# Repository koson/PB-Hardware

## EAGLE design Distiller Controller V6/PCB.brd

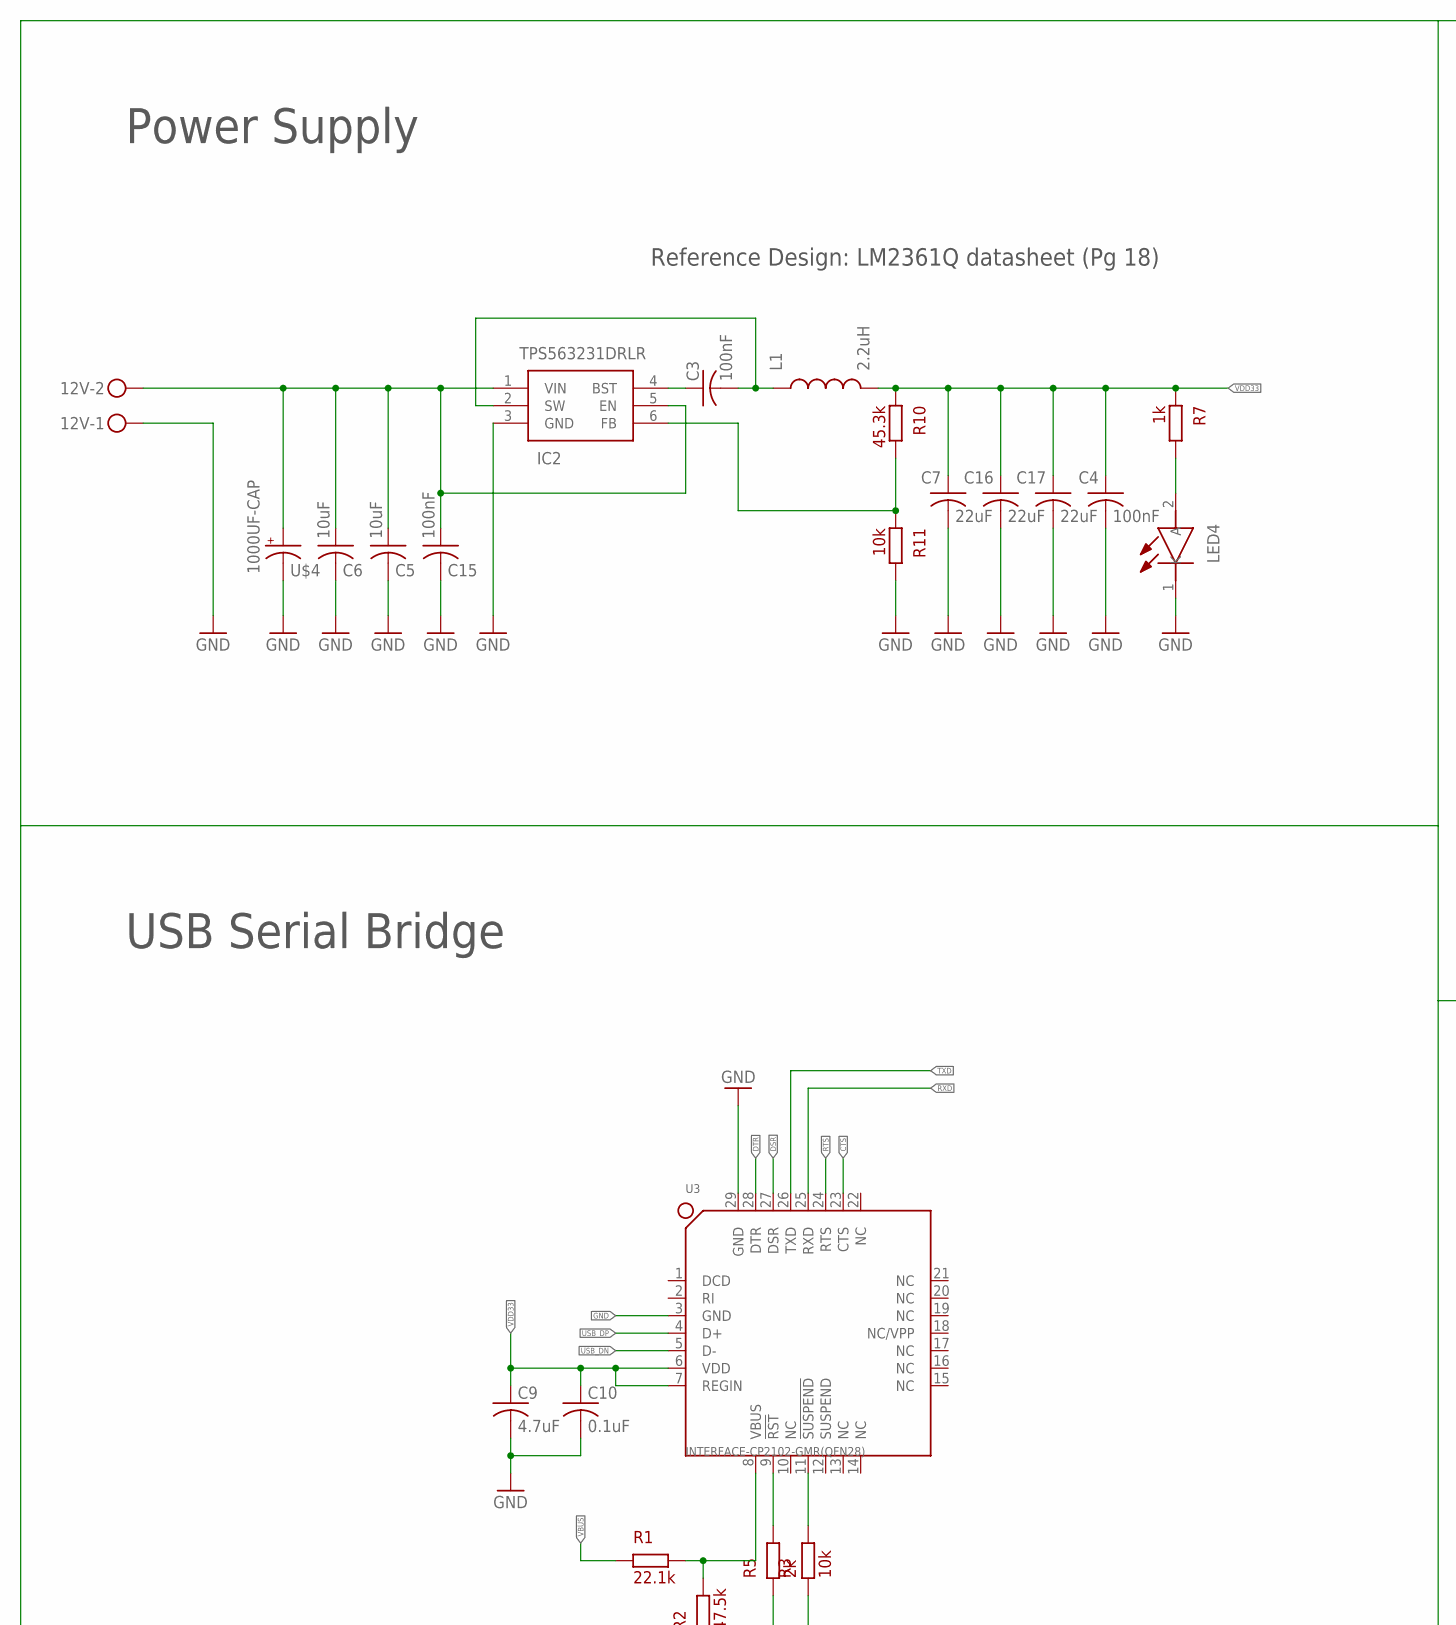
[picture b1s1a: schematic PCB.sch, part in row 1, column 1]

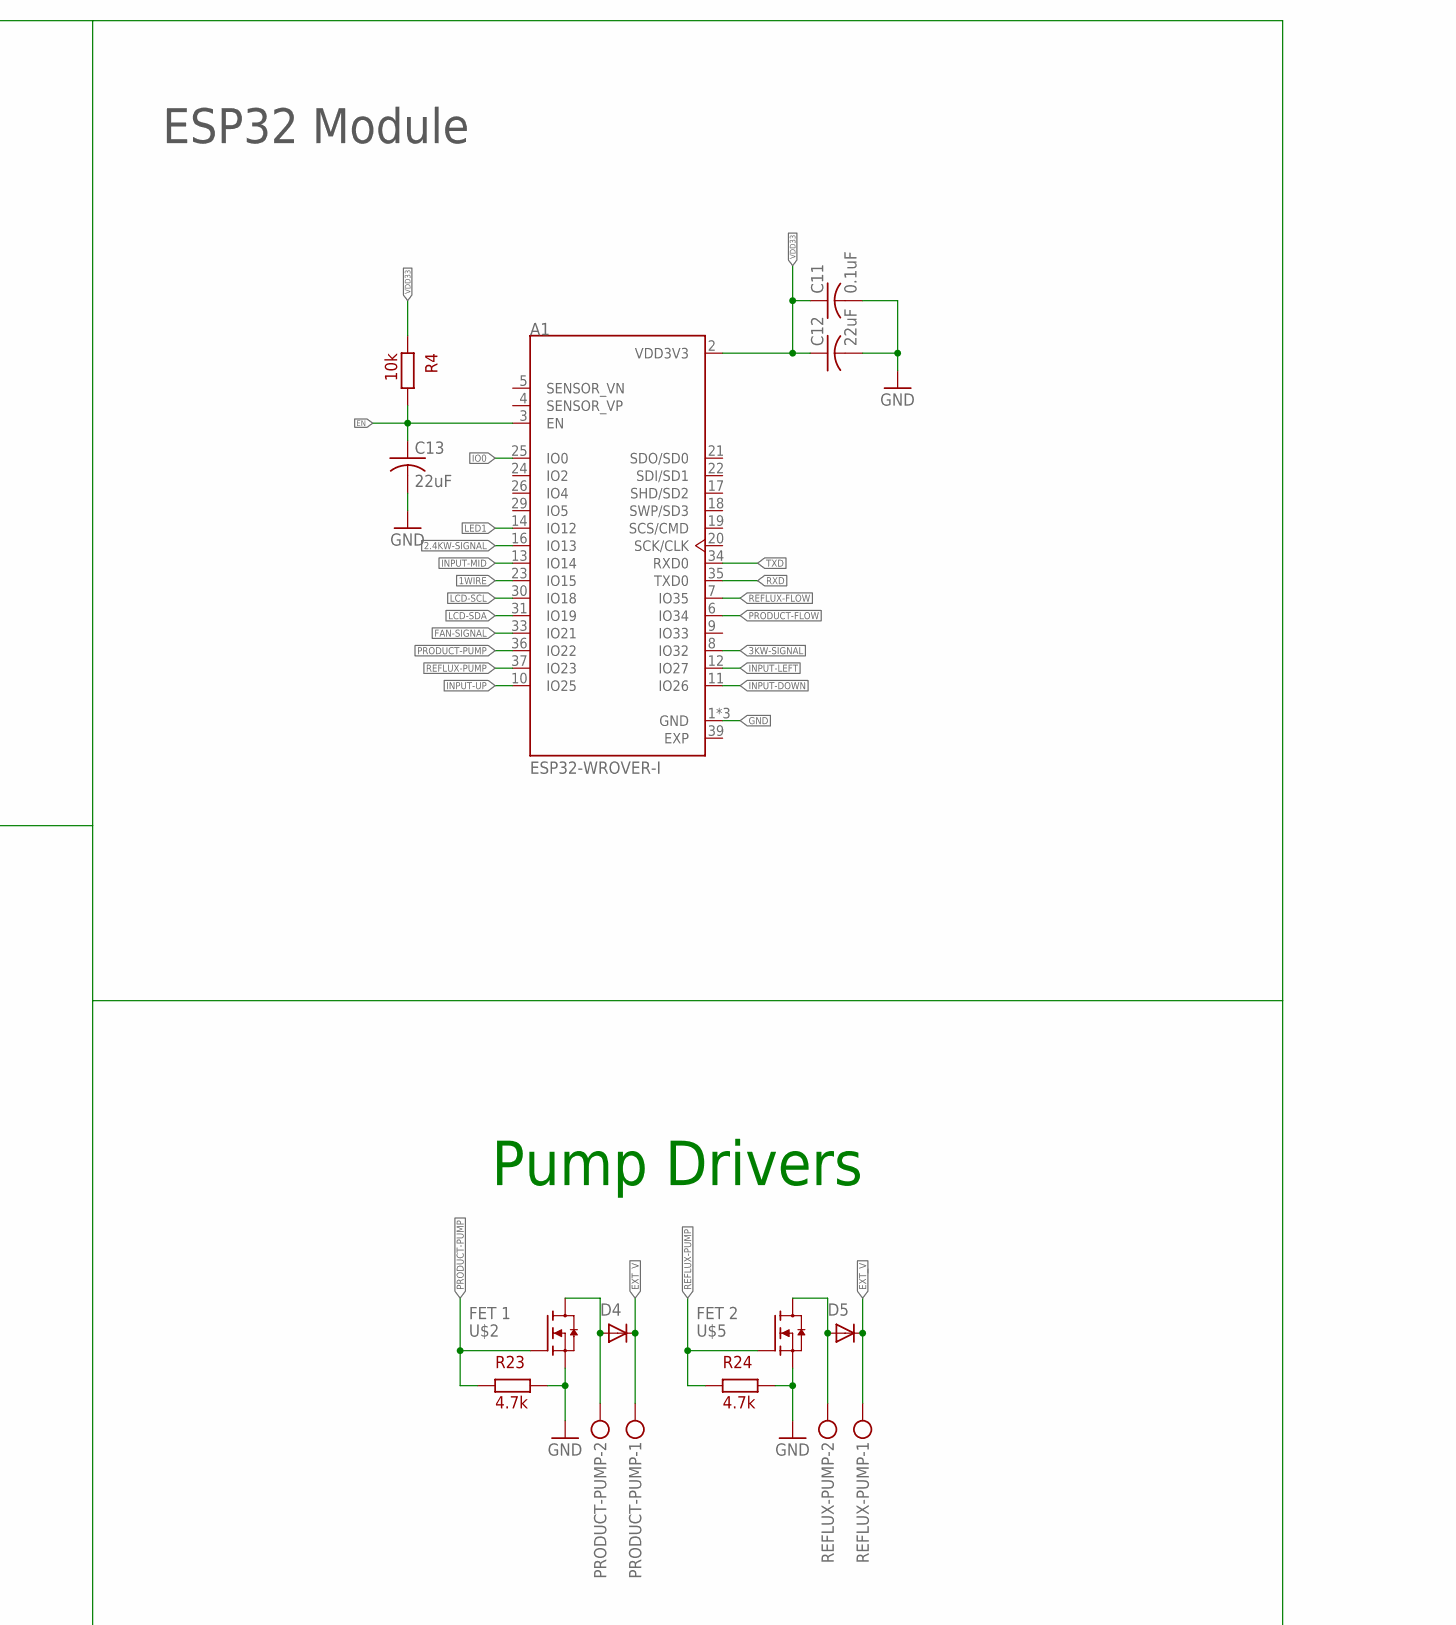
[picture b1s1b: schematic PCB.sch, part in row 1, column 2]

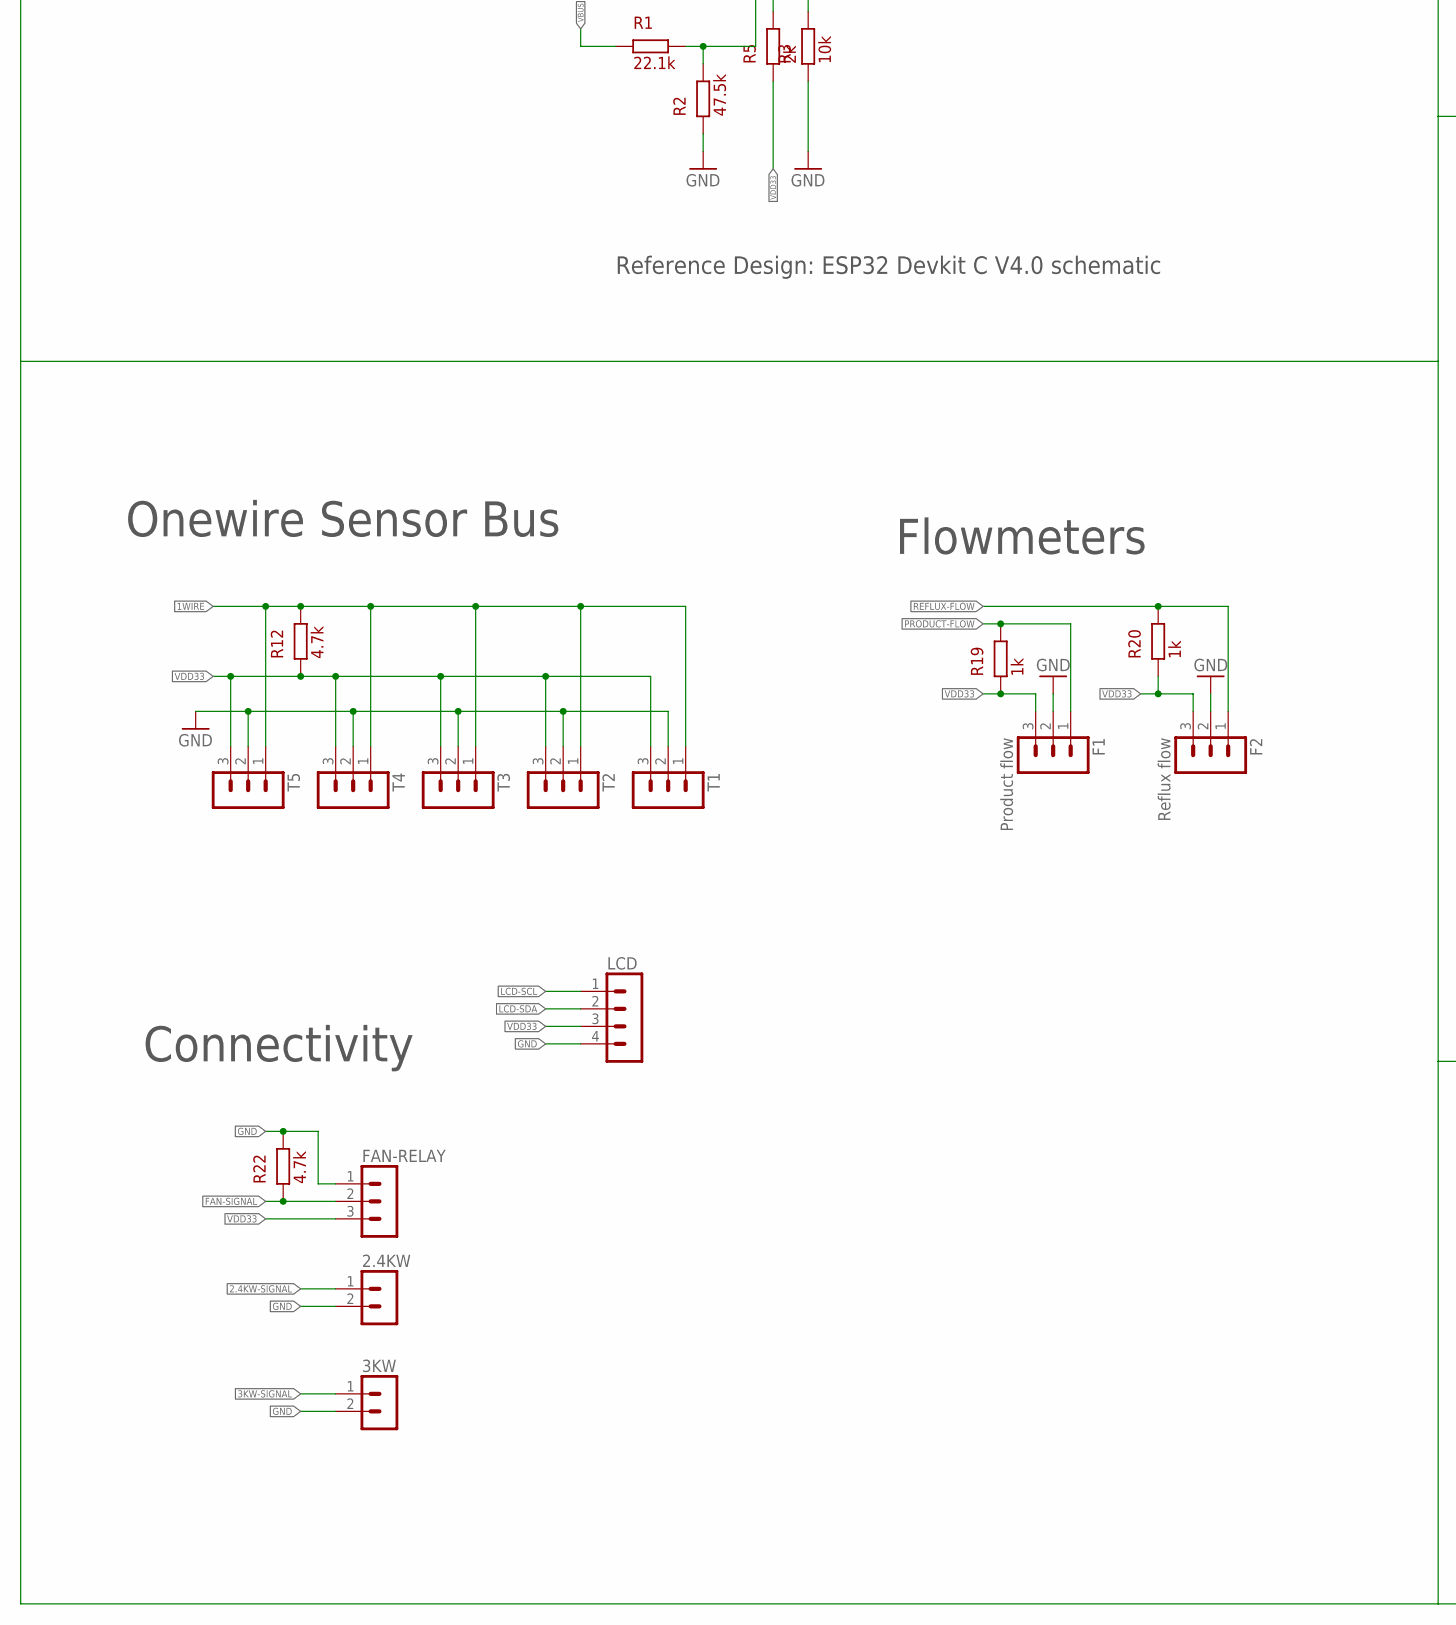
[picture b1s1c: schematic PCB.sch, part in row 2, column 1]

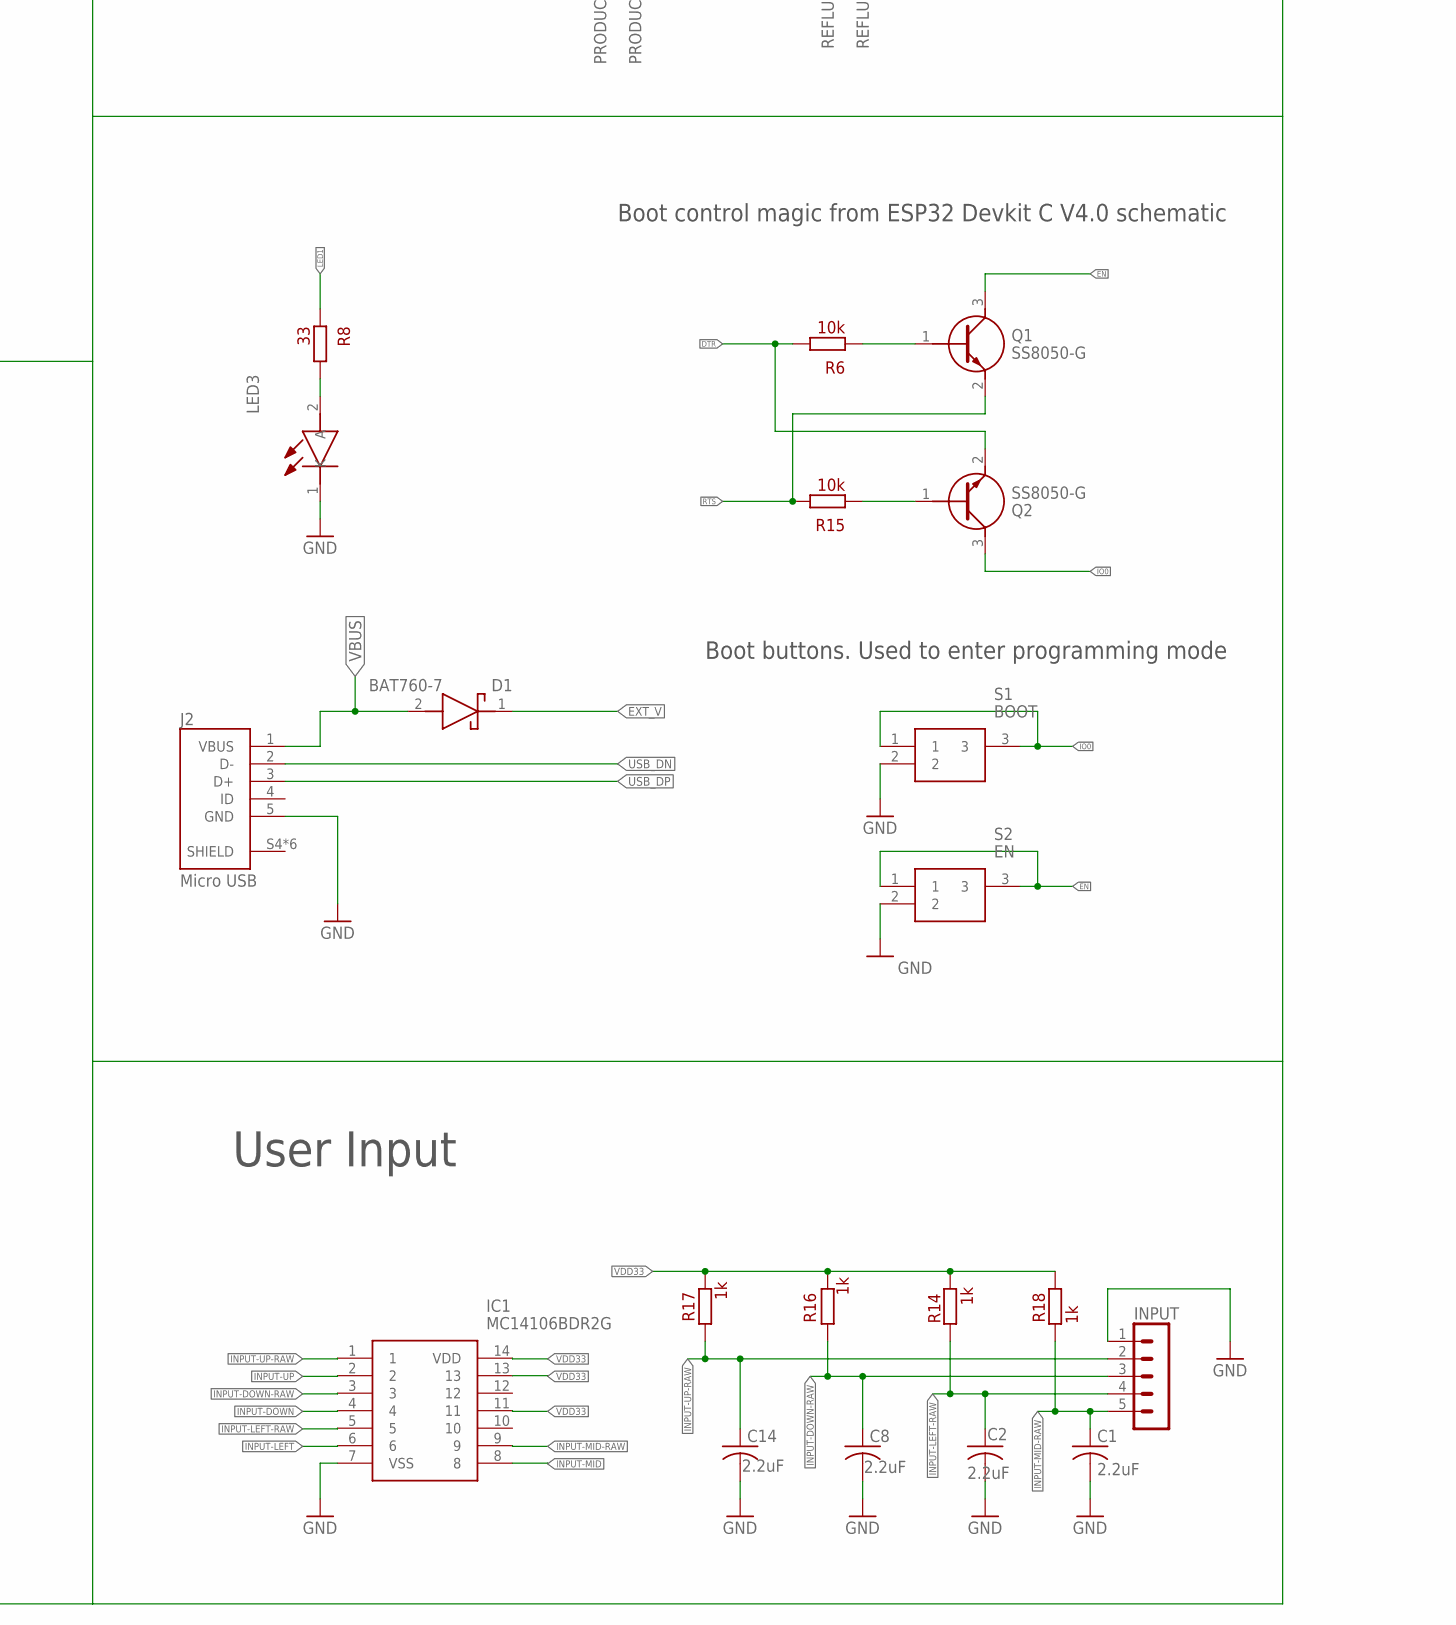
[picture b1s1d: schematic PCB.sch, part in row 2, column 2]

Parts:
2.4KW, 3KW: 53398-0210
12V: MKDSN1,5/2-5,08
A1: ESP32-WROVER-I; XCVR_ESP32-WROVER-I
C1, C2, C8, C14: 2.2uF; C0805K
C3, C4, C15: 100nF; C0805K
C5, C6: 10uF; C0805K
C7, C12, C13, C16, C17: 22uF; C0805K
C9: 4.7uF; C0805K
C10, C11: 0.1uF; C0805K
D1: BAT760-7; SOD2513X120N
D4, D5: RB095BGE-40TL; TO252; MPN PWR163S-25-2R20JE
F1: Product flow; 53398-0310
F2: Reflux flow; 53398-0310
FAN-RELAY: 53398-0310
IC1: MC14106BDR2G; SOIC127P600X175-14N
IC2: TPS563231DRLR; SOTFL50P160X60-6N
INPUT: 53398-0510
J2: Micro USB; TE_2040002-1
L1: 2.2uH; LB3218T2R2M
LCD: 53398-0410
LED3, LED4: SML-H12V8TT86C; LEDC2012X80N
PRODUCT-PUMP: MKDSN1,5/2-5,08
Q1, Q2: SS8050-G; SOT95P240X115-3N
R1: 22.1k; C0805K
R2: 47.5k; C0805K
R3, R4, R6, R11, R15: 10k; C0805K
R5: 2k; C0805K
R7, R14, R16, R17, R18, R19, R20: 1k; C0805K
R8: 33; C0805K
R10: 45.3k; C0805K
R12, R22, R23, R24: 4.7k; C0805K
REFLUX-PUMP: MKDSN1,5/2-5,08
S1: BOOT; TL3340
S2: EN; TL3340
T1, T2, T3, T4, T5: 53398-0310
U3: INTERFACE-CP2102-GMR(QFN28); QFN28G_0.5-5X5MM
U$2: FET 1; TO252
U$4: 1000UF-CAP; UNITED-CHEMICON-SMD-CAP-1000UF
U$5: FET 2; TO252

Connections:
1WIRE: A1.23 (IO15), R12.2, T1.1, T2.1, T3.1, T4.1, T5.1
2.4KW-SIGNAL: 2.4KW.1, A1.16 (IO13)
3KW-SIGNAL: 3KW.1, A1.8 (IO32)
BST: C3.1, IC2.4 (BST)
CTS: U3.23 (CTS)
DSR: U3.27 (DSR)
DTR: Q2.2 (E), R6.2, U3.28 (DTR)
EN: A1.3 (EN), C13.1, Q1.3 (C), R4.2, S2.1, S2.3
EXP: A1.39 (EXP)
EXT_V: 12V.2, C5.1, C6.1, C15.1, D1.1 (K), D4.2 (C), D5.2 (C), IC2.1 (VIN), IC2.5 (EN), PRODUCT-PUMP.1, REFLUX-PUMP.1, U$4.+
FAN-SIGNAL: A1.33 (IO21), FAN-RELAY.2, R22.1
GND: 2.4KW.2, 3KW.2, 12V.1, A1.1 (GND), A1.15 (GND), A1.38 (GND), C1.2, C2.2, C4.2, C5.2, C6.2, C7.2, C8.2, C9.2, C10.2, C11.2, C12.2, C13.2, C14.2, C15.2, C16.2, C17.2, F1.2, F2.2, FAN-RELAY.1, IC1.7 (VSS), IC2.3 (GND), INPUT.1, J2.5 (GND), LCD.4, LED3.1 (K), LED4.1 (K), R2.1, R3.1, R11.2, R22.2, R23.2, R24.2, S1.2, S2.2, T1.2, T2.2, T3.2, T4.2, T5.2, U3.3 (GND), U3.29 (GND), U$2.3 (S), U$4.-, U$5.3 (S)
INPUT-DOWN: A1.11 (IO26), IC1.4
INPUT-DOWN-RAW: C8.1, IC1.3, INPUT.3, R16.1
INPUT-LEFT: A1.12 (IO27), IC1.6
INPUT-LEFT-RAW: C2.1, IC1.5, INPUT.4, R14.1
INPUT-MID: A1.13 (IO14), IC1.8
INPUT-MID-RAW: C1.1, IC1.9, INPUT.5, R18.1
INPUT-UP: A1.10 (IO25), IC1.2
INPUT-UP-RAW: C14.1, IC1.1, INPUT.2, R17.1
IO0: A1.25 (IO0), Q2.3 (C), S1.1, S1.3
LCD-SCL: A1.30 (IO18), LCD.1
LCD-SDA: A1.31 (IO19), LCD.2
LED1: A1.14 (IO12), R8.1
unnamed: R3.2, U3.11 (!SUSPEND)
unnamed: R5.2, U3.9 (!RST)
unnamed: R1.2, R2.2, U3.8 (VBUS)
unnamed: LED4.2 (A), R7.2
unnamed: LED3.2 (A), R8.2
unnamed: IC2.6 (FB), R10.2, R11.1
unnamed: D4.1 (A), D4.3 (A), PRODUCT-PUMP.2, U$2.2 (D)
unnamed: D5.1 (A), D5.3 (A), REFLUX-PUMP.2, U$5.2 (D)
unnamed: Q1.1 (B), R6.1
unnamed: Q2.1 (B), R15.1
PRODUCT-FLOW: A1.6 (IO34), F1.1, R19.2
PRODUCT-PUMP: A1.36 (IO22), R23.1, U$2.1 (G)
REFLUX-FLOW: A1.7 (IO35), F2.1, R20.2
REFLUX-PUMP: A1.37 (IO23), R24.1, U$5.1 (G)
RTS: Q1.2 (E), R15.2, U3.24 (RTS)
RXD: A1.35 (TXD0), U3.25 (RXD)
SHIELD: J2.S4 (SHIELD), J2.S5 (SHIELD), J2.SH1 (SHIELD), J2.SH2 (SHIELD), J2.SH3 (SHIELD), J2.SH4 (SHIELD)
SW: C3.2, IC2.2 (SW), L1.P$1 (1)
TXD: A1.34 (RXD0), U3.26 (TXD)
USB_DN: J2.2 (D-), U3.5 (D-)
USB_DP: J2.3 (D+), U3.4 (D+)
VBUS: D1.2 (A), J2.1 (VBUS), R1.1
VDD33: A1.2 (VDD3V3), C4.1, C7.1, C9.1, C10.1, C11.1, C12.1, C16.1, C17.1, F1.3, F2.3, FAN-RELAY.3, IC1.11, IC1.13, IC1.14 (VDD), L1.P$2 (2), LCD.3, R4.1, R5.1, R7.1, R10.1, R12.1, R14.2, R16.2, R17.2, R18.2, R19.1, R20.1, T1.3, T2.3, T3.3, T4.3, T5.3, U3.6 (VDD), U3.7 (REGIN)

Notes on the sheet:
Reference Design: LM2361Q datasheet (Pg 18)
Reference Design: ESP32 Devkit C V4.0 schematic
ESP32 Module
Boot control magic from ESP32 Devkit C V4.0 schematic
Boot buttons. Used to enter programming mode
Power Supply
USB Serial Bridge
Onewire Sensor Bus
Connectivity
Flowmeters
Pump Drivers
User Input

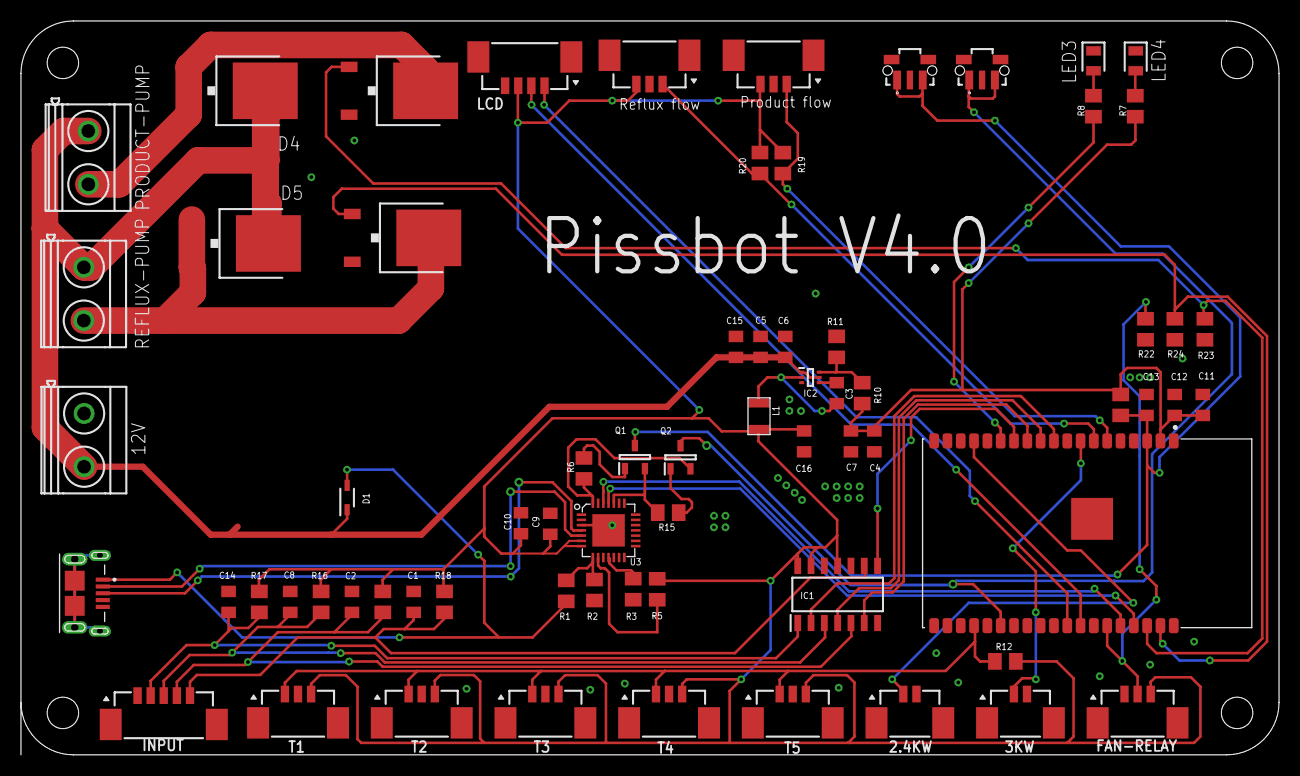
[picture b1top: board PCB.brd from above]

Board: 2 copper layers, 120.0 x 70.0 mm, 69 parts (0 on the bottom side), 44 nets.

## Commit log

2020-10-26 Updated PCB
2020-11-22 Updated PCB. Added library files
2022-02-16 Save
2022-08-18 test

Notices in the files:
parts and their libraries:
con-molex-picoblade: Copyright (C) 2010, Bob Starr
